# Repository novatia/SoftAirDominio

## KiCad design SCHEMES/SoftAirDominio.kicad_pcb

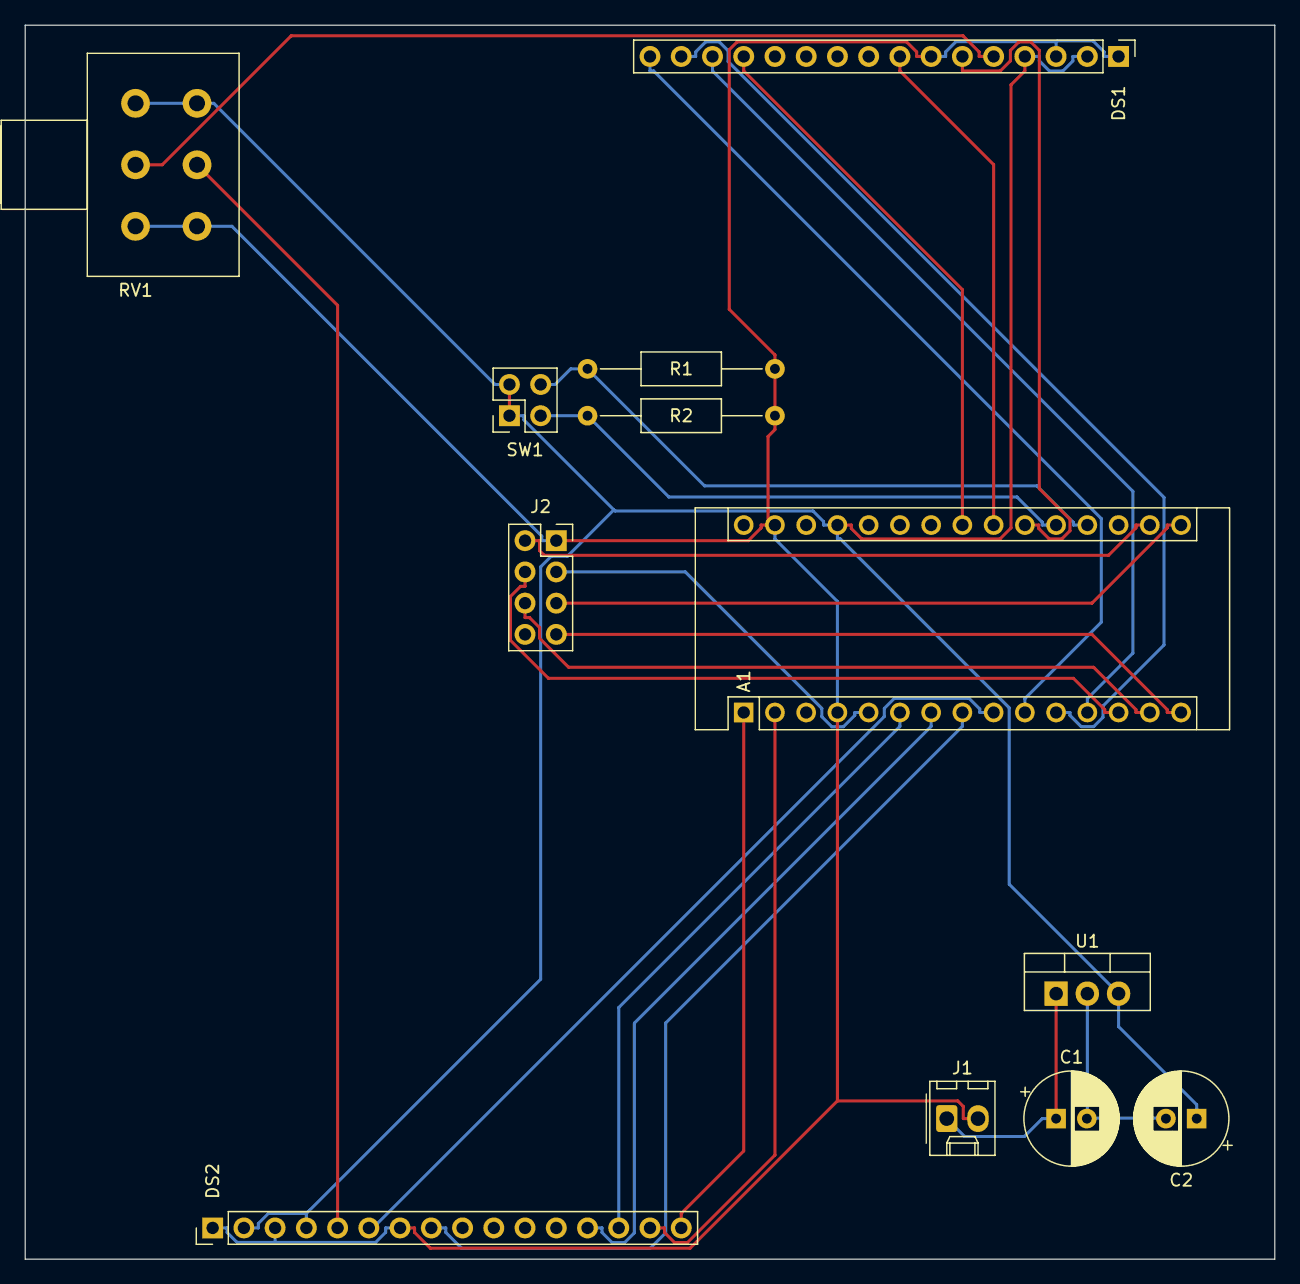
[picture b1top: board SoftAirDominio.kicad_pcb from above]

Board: 2 copper layers, 101.6 x 100.3 mm, 12 parts (0 on the bottom side), 26 nets.

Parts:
A1: Arduino_Nano_v3.x; Arduino_Nano
C1, C2: 57uF 16V; CP_Radial_D7.5mm_P2.50mm
DS1, DS2: HY1602E; PinHeader_1x16_P2.54mm_Vertical
J1: 9V Battery; Molex_KK-254_AE-6410-02A_1x02_P2.54mm_Vertical
J2: C1101; PinSocket_2x04_P2.54mm_Vertical
R1, R2: 1k; R_Axial_DIN0207_L6.3mm_D2.5mm_P15.24mm_Horizontal
RV1: 10k; Potentiometer_Alps_RK163_Dual_Horizontal
SW1: SW_Push_Dual; PinSocket_2x02_P2.54mm_Vertical
U1: L7805; TO-220-3_Vertical

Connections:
+5V: A1.27, C2.1, DS1.2, DS1.4, DS2.2, DS2.4, RV1.1, RV1.4, SW1.1, SW1.3, U1.3
+9V: C1.1, J1.1, U1.1
GND: A1.4, A1.29, DS1.1, DS1.3, DS1.7, DS2.1, DS2.3, DS2.7, J1.2, J2.1, R1.2, R2.2, RV1.3, RV1.6
unnamed: A1.1, DS2.16
unnamed: A1.2, DS2.15
unnamed: A1.5, J2.3
unnamed: A1.6, DS2.14
unnamed: A1.7, DS2.13
unnamed: A1.8, DS2.8
unnamed: A1.9, DS2.6
unnamed: A1.10, DS1.16
unnamed: A1.11, DS1.15
unnamed: A1.12, DS1.14
unnamed: A1.13, J2.4
unnamed: A1.14, J2.6
unnamed: A1.15, J2.7
unnamed: A1.16, J2.5
unnamed: A1.17, J2.2
unnamed: A1.19, R1.1, SW1.4
unnamed: A1.20, R2.1, SW1.2
unnamed: A1.21, DS1.6
unnamed: A1.22, DS1.8
unnamed: A1.23, DS1.13
unnamed: C1.2, C2.2, U1.2
unnamed: DS1.5, RV1.2
unnamed: DS2.5, RV1.5

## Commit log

2023-09-11 first import
2023-09-11 added kicad schemes
